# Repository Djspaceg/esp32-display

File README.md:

# esp32-display

Turn supported ESP32 display boards into small wireless displays driven by a
native macOS app. The repository contains firmware, wire protocols, a signed-app
build, USB onboarding, OTA updates, and canonical precompiled releases.

## What it does

- Streams dirty RGB565 bands or tiles over UDP.
- Uses packed/RLE bands on smaller displays, tile codecs on the 466×466 round
  AMOLED, and capability-gated ETL1 large tiles on 720×720 P4.
- Discovers panels through `_espdisp._udp` mDNS records.
- Supports brightness, power, rotation, identify, restart, touch gestures,
  battery telemetry, status screens, and password-protected OTA.
- Onboards blank boards over USB with explicit identity checks.
- Packages current firmware as one artifact per chip family.

## Firmware families

Release families are exactly `c3`, `c6`, `s3`, and `p4`. Every family is universal
within its currently supported chip-family profiles. Product names, panel names,
and internal build-target keys are not release names.

| Family | Chip | Runtime profiles | Canonical partition |
| --- | --- | --- | --- |
| `c6` | `esp32c6` | `st7789`, `jd9853` | `default-8m` |
| `s3` | `esp32s3` | `st7735-042`, `gc9107`, `st7789-130`, `st7789-154`, `st7789-190`, `co5300`, `st77916`, `gc9a01-knob-128`, `st7789-twatch` | `universal-8m-doom-saves-ota` |
| `p4` | `esp32p4` | `st7703-4b`, `jd9365-4c`, `jd9365-34c` | `p4-32m-saves-ota` |

The S3 image uses an 8 MiB common-denominator dual-OTA layout and contains all
supported S3 panel, touch, power, and peripheral paths, including the
runtime-gated Doom easter egg for the CO5300 (`co5300`) profile. Doom's heavy
renderer state and mutable engine tables allocate from PSRAM only when it
starts, so normal streaming keeps the internal RAM its SPI DMA rotation repaint
needs. The canonical artifact and app resources carry Doom code but no WAD; the
WAD stays a developer-installed payload read from a raw flash region on the
16/32 MiB CO5300 carrier.

P4 keeps platform, internal build-target, panel, and carrier configuration
separate. The P4 platform owns chip/toolchain/memory/network facts; the internal
composition owns its family selector and partition source; the ST7703 and
JD9365 panel profiles own their MIPI timing; and each carrier profile owns its
GPIOs, GT911, and backlight wiring. The released artifact remains named only
`p4`.

See [firmware family architecture](docs/firmware-target-architecture.md).

## Supported boards

Every board this firmware runs on, and what each one supports. "Square" is a
functional property, not cosmetic: it decides whether the IMU can drive all four
orientations or only a 180-degree flip.

| Runtime profile | Board | Chip | Panel | Resolution | Diagonal | Square | IMU | Automatic orientation | Orientations in the app | Audio |
| --- | --- | --- | --- | --- | --- | --- | --- | --- | --- | --- |
| `st7789` | [ESP32-C6-LCD-1.47](https://www.waveshare.com/esp32-c6-lcd-1.47.htm) | `esp32c6` | ST7789 | 172x320 | 1.47" | No | No | None | 0/180 | None |
| `jd9853` | [ESP32-C6-Touch-LCD-1.47](https://www.waveshare.com/esp32-c6-touch-lcd-1.47.htm) | `esp32c6` | JD9853 | 172x320 | 1.47" | No | Yes | Flip only (0/180) | 0/180 | None |
| `st7735-042` | [Seeed XIAO ESP32-S3](https://wiki.seeedstudio.com/xiao_esp32s3_getting_started/) + [Questwise 0.42" 96x54 TFT](https://github.com/questwiseventures/TFT_ST7735_96x54_Color_TFT) | `esp32s3` | ST7735 | 96x54 | 0.42" | No | No | None | 0/90/180/270 | None |
| `gc9107` | [ESP32-S3-LCD-0.85](https://www.waveshare.com/esp32-s3-lcd-0.85.htm) | `esp32s3` | GC9107 | 128x128 | 0.85" | Yes | No | None | 0/90/180/270 | Speaker + mic |
| `st7789-130` | [ESP32-S3-LCD-1.3](https://www.waveshare.com/esp32-s3-lcd-1.3.htm) | `esp32s3` | ST7789V2 | 240x240 | 1.3" | Yes | Yes | Four-way | 0/90/180/270 | None |
| `st7789-154` | [ESP32-S3-LCD-1.54](https://www.waveshare.com/esp32-s3-lcd-1.54.htm) | `esp32s3` | ST7789 | 240x240 | 1.54" | Yes | Yes | Four-way | 0/90/180/270 | Speaker + 2 mics |
| `st7789-190` | [ESP32-S3-LCD-1.9](https://docs.waveshare.com/ESP32-S3-LCD-1.9) | `esp32s3` | ST7789V2 | 170x320 | 1.9" | No | Yes | Flip only (0/180) | 0/180 | None |
| `co5300` | [ESP32-S3-Touch-AMOLED-1.75C](https://www.waveshare.com/esp32-s3-touch-amoled-1.75c.htm) | `esp32s3` | CO5300 (AMOLED) | 466x466 | 1.75" | Yes | Yes | Four-way | 0/90/180/270 | Speaker + 2 mics |
| `st77916` | [ESP32-S3-Touch-LCD-1.85C](https://www.waveshare.com/esp32-s3-touch-lcd-1.85c.htm) | `esp32s3` | ST77916 (round) | 360x360 | 1.85" | Yes | No | None | 0/90/180/270 | Speaker + 2 mics (V2; V1 stays off) |
| `gc9a01-knob-128` | [ELECROW CrowPanel 1.28" Rotary Display](https://github.com/Elecrow-RD/CrowPanel-1.28inch-HMI-ESP32-Rotary-Display-240-240-IPS-Round-Touch-Knob-Screen) | `esp32s3` | GC9A01 (round) | 240x240 | 1.28" | Yes | No | None | 0/90/180/270 | None |
| `st7789-twatch` | [LilyGO T-Watch-S3](https://wiki.lilygo.cc/products/t-watch-series/t-watch-s3/) | `esp32s3` | ST7789V3 | 240x240 | 1.54" | Yes | BMA4xx, no driver here | None | 0/90/180/270 | Speaker + PDM mic, not driven here |
| `st7703-4b` | [ESP32-P4-WIFI6-Touch-LCD-4B](https://www.waveshare.com/esp32-p4-wifi6-touch-lcd-4b.htm) | `esp32p4` | ST7703 (MIPI-DSI) | 720x720 | 4" | Yes | No | None | 0/90/180/270 | Speaker + 2 mics |
| `jd9365-4c` | [ESP32-P4-WIFI6-Touch-LCD-4C](https://www.waveshare.com/wiki/ESP32-P4-WIFI6-Touch-LCD-4C) | `esp32p4` | JD9365 (MIPI-DSI, round) | 720x720 | 4" | Yes | No | None | 0/90/180/270 | Speaker + 2 mics |
| `jd9365-34c` | [ESP32-P4-WIFI6-Touch-LCD-3.4C](https://www.waveshare.com/wiki/ESP32-P4-WIFI6-Touch-LCD-3.4C) | `esp32p4` | JD9365 (MIPI-DSI, round) | 800x800 | 3.4" | Yes | No | None | 0/90/180/270 | Speaker + 2 mics |

The Audio column is the vendor hardware, sourced in each board's descriptor.
Every audio board uses ES8311 (speaker, via an NS4150B amplifier) and ES7210
(microphones), and firmware turns audio on only after both chips answer with
their chip IDs over I2C. On the 1.85C that is what separates V2 from V1, whose
different audio parts stay off. The C3 board has no audio.

Orientation rules behind the Square, IMU and orientation columns:

- A square panel with an IMU auto-rotates through all four cardinal
  orientations.
- A non-square panel with an IMU auto-flips between 0 and 180 only. A
  quarter-turn is never applied automatically, because the quarter-turn
  framebuffer geometry for non-square panels is intentionally unsupported.
  Side-pointing gravity holds the last stable 0 or 180 rather than guessing a
  nearest edge, and only a settled up/down reading commits a change.
- A board with no IMU never rotates on its own, but its orientation is still
  selectable from the macOS app.
- A manual choice is never overwritten. Effective rotation is
  `(manual + automatic) mod 4`: the app writes the saved rotation, gravity moves
  only a volatile correction on top of it.

Axis calibration is not uniform. Two profiles are field-verified, each checked in
all four cable positions on real hardware: `co5300` (panel X = raw Y, panel Y =
raw X, neither negated) and `st7789-154` (the vendor's identity axes, confirmed
correct as shipped rather than assumed). `st7789-130`, `st7789-190` and `jd9853` still use the
vendor example's identity axes with no calibration run behind them, so their
automatic orientation may be correctly shaped but wrongly signed until one is
done. Two positions is not a calibration: a single inverted sign leaves one
opposite pair correct and only the other pair wrong, which is how a wrong
mapping survived several confirmations here.

Board identity, pin maps, panel geometry, and motion mappings are declared in
[`boards/*.toml`](boards/); those descriptors are the source of truth if this
table or generated firmware data drifts.

## Runtime profile selection

Profile selection occurs before panel GPIO initialization.

- C6 probes the shared GPIO18/19 I2C bus. A responding touch/motion path selects
  `jd9853`; a silent bus selects `st7789`. An inconclusive C6 probe uses the
  electrically safer profile.
- On 8 MiB S3 parts the probe is the 0.85's codec bus (ES8311 `0x18`, ES7210
  `0x40` on GPIO42/41): an answer selects `gc9107`, silence `st7735-042` (the
  XIAO has nothing on those pads and its screen cannot be read back). S3 then
  probes distinct I2C buses on larger-flash carriers. The `st7789-130` profile uses the
  QMI8658A at `0x6B` on GPIO47/48 and routes CFG commands through its CH343
  UART bridge; existing S3 profiles retain native USB CDC. The `st7789-190`
  carrier answers identically on GPIO47/48, so both profiles also read GPIO4
  with the pull-down enabled: the 1.9's system-rail divider reads at least
  250 mV and the 1.3's bare header pin at most 150 mV. The
  `gc9a01-knob-128` profile powers its GPIO1-switched panel rail for the probe
  and looks for its CST816D at `0x15` on GPIO6/7. The `st7789-twatch` watch
  answers on its always-powered main bus, SDA GPIO10 / SCL GPIO11 (AXP2101
  `0x34`, BMA4xx `0x19`, PCF8563 `0x51`), probed before the 1.75C's and the
  knob's buses. Its panel, backlight and touch run from AXP2101 ALDO2/ALDO3,
  which panel bring-up sets to LilyGO's 3300 mV and switches on. Exactly one
  compatible candidate is required.
- P4's carriers wire identical I2C buses, so P4 needs signals that agree
  before choosing. It reads GPIO52 with the pull-down enabled (the 4B's
  Ethernet PHY pulls that MDIO line up with 1.5K; on the XC carrier of the 4C
  and 3.4C it is a floating header pin), the resolution stored in the GT9271
  touch controller's config (register `0x8048`, read-only), and its MIPI-DSI
  panel's controller ID (DCS `0x04`, with a one-second deadline). The 4B needs
  its ST7703's `38 21 1F` and a high GPIO52. The 4C needs its JD9365's
  `93 65 04`, a low GPIO52 and a 720x720 touch config; the 3.4C the same with
  an 800x800 one. Any disagreement, or a failed read, resolves neither, like
  an unresolved S3, and the backlight is switched off. An XC board with
  something on its header that pulls GPIO52 high is therefore Unknown; send
  `CFGBOARD jd9365-4c` (or `jd9365-34c`) over serial to pin it. The 3.4C
  profile comes from Waveshare's BSP and has not been run on 3.4C hardware.
  The internal family selector remains a build implementation detail and the
  artifact is `p4`.

Zero or multiple S3 or P4 candidates leave display, networking, and streaming
disabled. Serial remains active so `CFGBOARD <profile>` can provide an explicit
recovery override. `CFGBOARD auto` clears the override.

Current firmware reports independent identity evidence:

```text
target=c3|c6|s3|p4
chip=esp32c3|esp32c6|esp32s3|esp32p4
profile=<runtime profile>
partition=<compatibility token>
```

The Mac app requires all four fields to auto-select embedded firmware. Missing,
unknown, conflicting, or stale evidence fails closed.

## Canonical releases

Canonical firmware is committed under `firmware-releases/`:

```text
firmware-releases/manifest.json
firmware-releases/c6/espdisp-c6-<version>.espdispfw
firmware-releases/s3/espdisp-s3-<version>.espdispfw
firmware-releases/p4/espdisp-p4-<version>.espdispfw
```

The catalog lists each latest SemVer, relative path, SHA-256, byte size, chip,
profiles, hardware mappings, flash capacities, partition compatibility, flash
addresses, and required identity fields. Catalog and bundle readers reject
duplicate JSON member names.

A current `.espdispfw` contains one family only. Historical multi-target bundles
remain readable but current writers never produce one.

Generate all three build-numbered development artifacts and their local catalog:

```sh
python3 tools/espdisp.py release
```

This writes under the ignored `firmware-dev/` root. Build-numbered firmware is
never allowed under `firmware-releases/`, so a development run cannot replace
the committed shipping catalog with paths to ignored artifacts. Shipping cuts
use bare versions under `firmware-releases/` after the user bumps `FW_VERSION`;
the current build-numbered writer is development-only. An intentional rebuild
of an existing shipping version must confirm that exact version:

```sh
python3 tools/espdisp.py release --shipping --regenerate-existing 1.5.0
```

Without that confirmation, `release --shipping` refuses to replace committed
shipping artifacts.

Inspect each artifact independently:

```sh
python3 tools/espdisp.py bundle-info firmware-releases/c6/espdisp-c6-1.5.0.espdispfw
python3 tools/espdisp.py bundle-info firmware-releases/s3/espdisp-s3-2.1.0.espdispfw
python3 tools/espdisp.py bundle-info firmware-releases/p4/espdisp-p4-1.5.0.espdispfw
```

`bundle-info` reports release-note availability or count, never the prose.
`release-notes.md` at the repository root is the sole authored source for that
prose.

## Build firmware

Install `arduino-cli` and the Espressif Arduino core, then build by family:

```sh
python3 tools/espdisp.py compile --family c6
python3 tools/espdisp.py compile --family s3
python3 tools/espdisp.py compile --family p4
```

The CLI stages custom partition files in private temporary sketch copies. It
does not mutate `firmware/display_stream/partitions.csv`.

## Flash over USB

List connected ports and optionally probe chip identity:

```sh
python3 tools/espdisp.py list --probe
```

Flash one family. Supplying `--port` is required when more than one candidate is
connected:

```sh
python3 tools/espdisp.py flash --family s3 --port /dev/cu.usbmodem1101
python3 tools/espdisp.py flash --family p4 --profile st7703-4b \
  --port /dev/cu.usbmodem5B901669681
```

`flash` verifies `firmware-releases/manifest.json` and writes the selected
committed family artifact. It does not compile mutable local source; use
`compile` or `bundle` explicitly for development builds.

The normal flash path writes only the bootloader, partition table, OTA
initializer, and application segments. It does not issue a whole-chip erase,
change fuses/security settings, or rewrite calibration data.

### Rescue a board that drops off USB

If firmware drives a board's own USB pins, the board shows up on USB for a
moment after each plug-in and then disappears, too briefly for `flash`. Unplug
it and run:

```sh
python3 tools/espdisp.py rescue --family s3
python3 tools/espdisp.py rescue --family p4 --profile jd9365-4c
```

As with `flash`, P4 needs `--profile` naming the carrier (`st7703-4b`,
`jd9365-4c` or `jd9365-34c`), because its image drives the display pins of any
P4 it lands on. The app's Repair flow asks for the board for the same reason.

Wait for "Plug the board in now", then plug it in; replug whenever it says
"Missed it". Only a port that appears after the command starts is touched. The
board then runs the rescue image from `firmware-rescue/<family>/`: it keeps USB
alive, never drives the USB pins, and shows RESCUE with the detected board name
on the panel. The ESP32-S3-LCD-1.3's backlight is on a USB pin, so its panel
stays dark. Follow up with `flash`. Rescue writes the bootloader, the release
partition table, the OTA selector and its own app, and nothing else, so NVS
settings and the Doom WAD survive. Rebuild a family's rescue image with
`rescue-build --family <family>` after changing the rescue sketch, board
detection or a panel profile.

A profile forced earlier with `CFGBOARD` is stored in NVS and would be forced
again by the real firmware. The rescue screen then shows it in red, and
`rescue` warns about it. Clear it before `flash` with
`python3 tools/espdisp.py config --port <port> CFGBOARD auto`, which the rescue
image answers by removing only that setting.

## Serial configuration

Send one `CFG*` command with the stdlib-only CLI:

```sh
python3 tools/espdisp.py config --port /dev/cu.usbmodem1101 CFGSHOW
python3 tools/espdisp.py config --port /dev/cu.usbmodem1101 CFGBOARD co5300
python3 tools/espdisp.py config --port /dev/cu.usbmodem1101 CFGPOWER 0
python3 tools/espdisp.py config --port /dev/cu.usbmodem1101 CFGROT 2
python3 tools/espdisp.py config --port /dev/cu.usbmodem1101 CFGAUTOROT 1
python3 tools/espdisp.py config --port /dev/cu.usbmodem1101 CFGMIRRORX 1
python3 tools/espdisp.py config --port /dev/cu.usbmodem1101 \
  CFGBRIGHTLEVELS 24 128 10 255
python3 tools/espdisp.py config --port /dev/cu.usbmodem1101 CFGFIXEDBL 255
python3 tools/espdisp.py config --port /dev/cu.usbmodem1101 CFGGAME QUAKE
python3 tools/espdisp.py config --port /dev/cu.usbmodem1101 CFGQUIET 1
```

`CFGAUTOROT 0|1` persists motion-based orientation; `CFGSHOW` reports both
`auto=` (the current motion correction) and `effective=` (the rotation actually
applied after composing it with `rot=`). `CFGBRIGHTLEVELS low high idle survey`
persists the four runtime brightness presets, each from 1 through 255, with
`low < high`.

`CFGMIRRORX` persists a left/right reflection for prism installations.
`CFGFIXEDBL 1..255` locks every lit state at that level and stops advertising
brightness controls; `CFGFIXEDBL 0` restores normal brightness behavior.

`CFGGAME <label>` starts a boot-menu row by its label (`DOOM`, `QUAKE`, a stored
WAD's name such as `FREEDOOM1`, or `STREAMING`), as choosing it on the menu
does. A game restarts the board into it, so it sends no reply; otherwise it
answers `CFGOK game=STREAMING`, `CFGERR the boot menu offers no <label>`, or
`CFGERR could not save the <label> request`. See `docs/game-store.md`.

`CFGQUIET 1` is quiet mode for benchmark and demo runs (`timedemo demo1`):
Doom and Quake start with no sound at all, effects or music, on every family
that runs them. It is persisted, so it lasts across restarts until
`CFGQUIET 0`, applies from the next game boot, and replies
`CFGOK quiet=1 (saved; Doom and Quake start with no sound)`. `CFGSHOW` reports
it as `quiet=`. A quiet game logs `sound: off, quiet mode` on serial and never
powers the codec or amplifier. Audio streamed from the Mac is not affected.

WiFi and names use base64-safe helper flows in the app. OTA stays disabled until
a password is stored:

```sh
python3 tools/espdisp.py set-password --port /dev/cu.usbmodem1101
```

## OTA

OTA requires live mDNS evidence for matching family, chip, profile, and
partition. Discovery cannot be disabled for a family-safe push.

```sh
export ESPDISP_OTA_PASSWORD='<password>'
python3 tools/espdisp.py ota panel.local --family s3
```

OTA writes the inactive application slot. It does not replace bootloader or
partition metadata. USB remains the recovery path.

The app updates a board that advertises `CAP_STREAM_UPDATE` over its existing
stream connection instead (`stream_update.h`, `StreamUpdateProtocol.swift`):
the same password and PBKDF2 challenge, a window of CRC-checked chunks with
selective acks, and the image's SHA-256 checked before `Update.end()` switches
the boot slot. The board never connects back to the Mac, so a Mac firewall that
drops connections from the LAN does not block it. Streaming to that board
pauses for the transfer. Boards without the bit, and the CLI, keep ArduinoOTA.

## macOS app

Build and install to `/Applications/ESPDisplay.app`:

```sh
mac/make-app.sh
```

The Xcode build phase validates `firmware-releases/manifest.json` and copies
exactly its latest c3/c6/s3/p4 artifacts directly into the app before signing. No
second repository copy exists under `mac/`.

A development fallback can build without firmware resources:

```sh
ESPDISP_SKIP_FIRMWARE=1 mac/make-app.sh
```

For a discovered panel, the update sheet auto-selects only from complete runtime
identity. For a blank/recovery board, the Add Display sheet requires an explicit
hardware-profile choice, then rechecks chip and MAC with esptool before writing.
Wrong family/chip/profile/partition, absent identity, ambiguous resources, and
catalog size/hash drift are refused.

A P4 or S3 display's Firmware section also has a **Games data** row. Its
**Install Game Data…** sheet adds Doom WADs and Quake paks to the board's game
store over USB: choose your own files or download Quake's shareware `pak0.pak`,
see which are already on the board and how much room is left, and write the
checked ones. See `docs/game-store.md`.

Release notes are rendered as literal text. Legacy bundles receive accessible
fallback text, and note metadata never affects transfer or update-safety logic.

## Protocols

### Band stream

The classic six-byte header contains frame ID, band index/orientation flags, and
dirty count. Packed datagrams may carry multiple raw or RLE565 bands.

### Tile stream

The CO5300 profile uses 16×16 dirty tiles with raw, RLE565, BC1, and
half-resolution BC1 codecs. Visible-span records avoid transmitting hidden
pixels outside round glass.

### ETL1 large tiles

The P4 profile advertises `CAP_LARGE_TILE_STREAM`. ETL1 uses 16-bit tile indices
for grids too large for tile v1. Records are validated and decoded before
completion state is committed, so malformed records can be retried without
poisoning frame state.

## P4 measured state

Attached revision-v1.3 hardware identified as ESP32-P4, base MAC
`e8:f6:0a:e0:b5:5a`, with 32 MiB flash. Display diagnostics measured correct
RGB primaries, edges/corners, full and partial draws, four software transforms,
GT911 portrait markers/releases, BOOT rotation, and backlight controls with no
draw errors.

Hosted networking remains blocked at `Req_GetCoprocessorFwVersion` with the
factory C6 image. The C6 coprocessor has not been modified and is not
electrically accessible through the current authorized development path.
Reachable mDNS, ETL1 over WiFi, reconnect, OTA, motion tearing, and touch corners
in odd orientations remain unverified.

## Repository layout

| Path | Purpose |
| --- | --- |
| `firmware/display_stream/` | Main universal-family firmware |
| `firmware/libraries/espdisp_board/` | Platform/panel/carrier composition and display facade |
| `firmware/test/` | Hardware-free ASan/UBSan host tests |
| `tools/espdisp.py` | Build, release, inspect, flash, OTA, and serial CLI |
| `tools/test_espdisp.py` | Python source/parser/writer/catalog tests |
| `firmware-dev/` | Ignored build-numbered artifacts and local catalog |
| `firmware-releases/` | Canonical committed family artifacts and catalog |
| `firmware-rescue/` | Prebuilt rescue images, one per family (`firmware/rescue/`) |
| `mac/ESPDisplaySender/` | Native app, protocol readers, and Swift tests |
| `docs/firmware-target-architecture.md` | Family selection and extension rules |
| `docs/code-structure.md` | Module ownership |

## Validation

Run the complete source gate before release:

```sh
bash firmware/test/run_tests.sh
python3 tools/test_espdisp.py
python3 tools/espdisp.py compile --family c6
python3 tools/espdisp.py compile --family s3
python3 tools/espdisp.py compile --family p4
```

From `mac/ESPDisplaySender`, run `swift test`. After generating canonical
artifacts, run `bundle-info` on all three, cross-read them with Swift tests,
build/install the signed app, and compare every embedded size/hash to the
catalog.

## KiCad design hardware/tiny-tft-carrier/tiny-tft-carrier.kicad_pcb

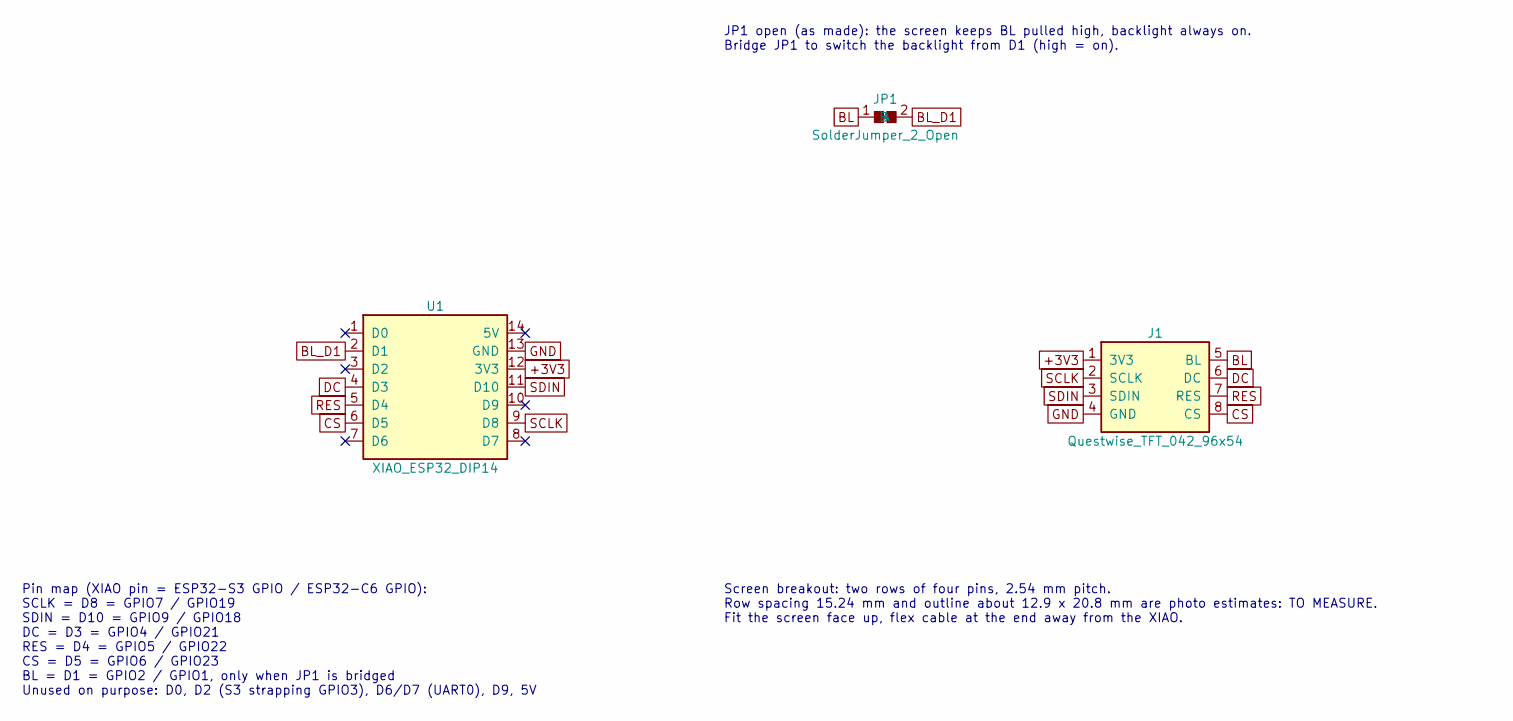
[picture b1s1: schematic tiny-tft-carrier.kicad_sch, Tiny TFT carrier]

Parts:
J1: Questwise_TFT_042_96x54; Questwise_TFT_042_96x54_2x4
JP1: SolderJumper_2_Open
U1: XIAO_ESP32_DIP14

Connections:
+3V3: J1.1 (3V3), U1.12 (3V3)
BL: J1.5 (BL), JP1.1 (A)
BL_D1: JP1.2 (B), U1.2 (D1)
CS: J1.8 (CS), U1.6 (D5)
DC: J1.6 (DC), U1.4 (D3)
GND: J1.4 (GND), U1.13 (GND)
RES: J1.7 (RES), U1.5 (D4)
SCLK: J1.2 (SCLK), U1.9 (D8)
SDIN: J1.3 (SDIN), U1.11 (D10)

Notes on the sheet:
Pin map (XIAO pin = ESP32-S3 GPIO / ESP32-C6 GPIO): SCLK = D8 = GPIO7 / GPIO19 SDIN = D10 = GPIO9 / GPIO18 DC = D3 = GPIO4 / GPIO21 RES = D4 = GPIO5 / GPIO22 CS = D5 = GPIO6 / GPIO23 BL = D1 = GPIO2 / GPIO1, only when JP1 is bridged Unused on purpose: D0, D2 (S3 strapping GPIO3), D6/D7 (UART0), D9,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
JP1 open (as made): the screen keeps BL pulled high, backlight always on. Bridge JP1 to switch the backlight from D1 (high = on).
Screen breakout: two rows of four pins, 2.54 mm pitch. Row spacing 15.24 mm and outline about 12.9 x 20.8 mm are photo estimates: TO MEASURE. Fit the screen face up, flex cable at the end away from the XIAO.

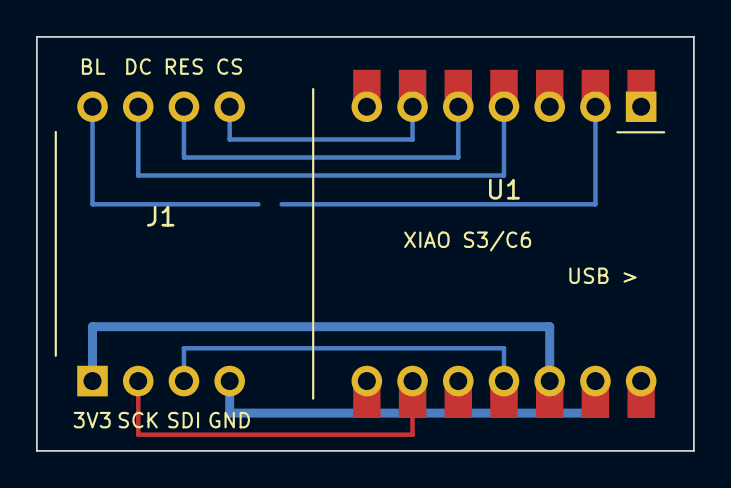
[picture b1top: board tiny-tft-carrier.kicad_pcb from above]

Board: 2 copper layers, 36.5 x 23.0 mm, 3 parts (1 on the bottom side), 9 nets.
